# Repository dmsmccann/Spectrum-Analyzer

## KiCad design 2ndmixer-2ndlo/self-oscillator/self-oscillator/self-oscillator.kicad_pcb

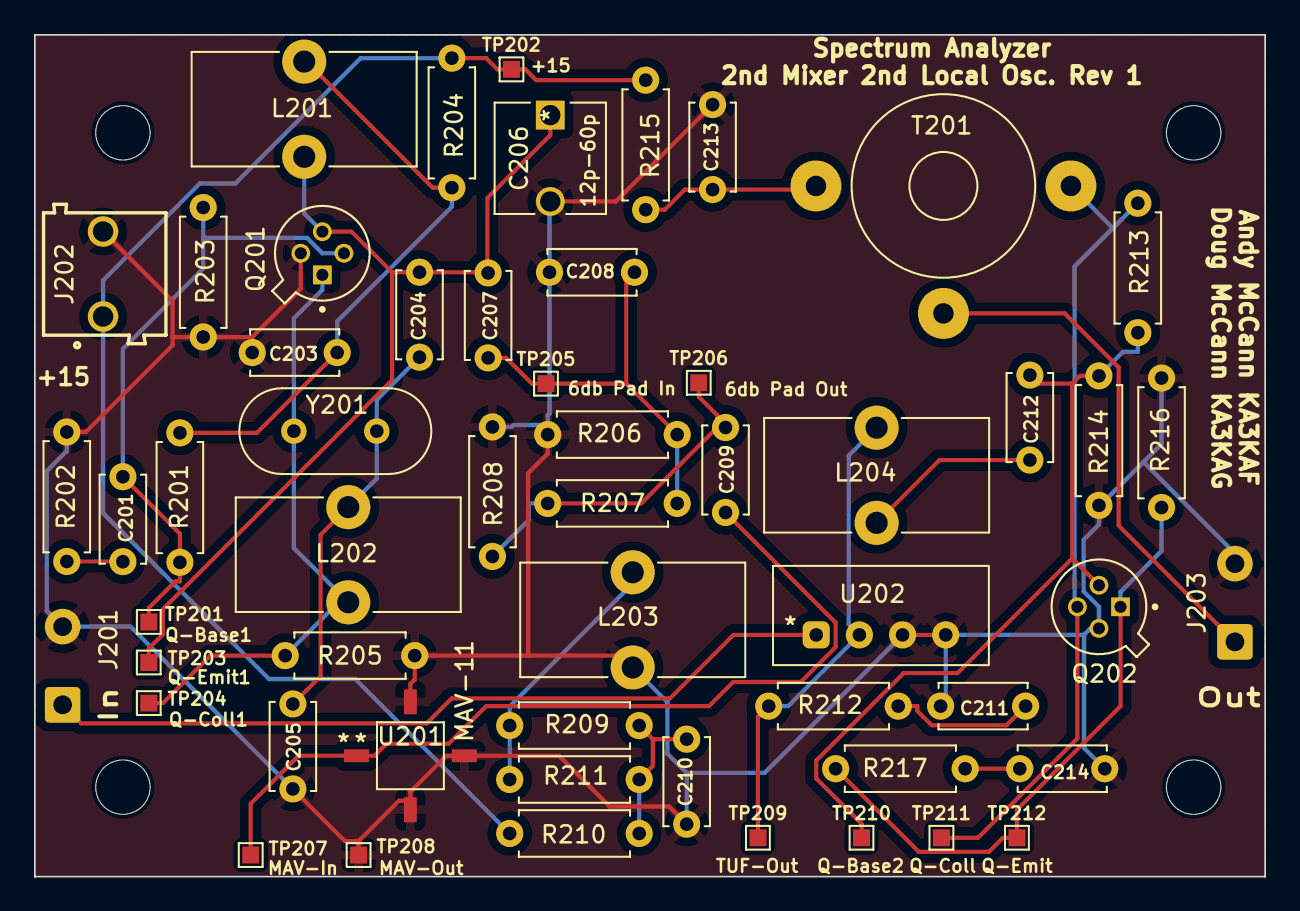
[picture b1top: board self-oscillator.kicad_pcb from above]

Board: 2 copper layers, 72.4 x 49.5 mm, 59 parts (0 on the bottom side), 23 nets.

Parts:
C201, C203: 470p; C_Disc_D5.0mm_W2.5mm_P5.00mm
C204, C205: 33p; C_Disc_D5.0mm_W2.5mm_P5.00mm
C206: 12p-60p; GKG60015
C207: 15p; C_Disc_D5.0mm_W2.5mm_P5.00mm
C208: 82p; C_Disc_D5.0mm_W2.5mm_P5.00mm
C209, C210: .01u; C_Disc_D5.0mm_W2.5mm_P5.00mm
C211: 120p; C_Disc_D5.0mm_W2.5mm_P5.00mm
C212, C213, C214: .1u; C_Disc_D5.0mm_W2.5mm_P5.00mm
H201, H202, H203, H204: MountingHole; MountingHole_3.2mm_M3
J201, J203: Coax Solder Point; SolderWire-0.5sqmm_1x02_P4.6mm_D0.9mm_OD2.1mm
J202: Conn_01x02; 691103110002
L201: 40n; L_Toroid_Vertical_L13.0mm_W6.5mm_P5.60mm
L202: 420n; L_Toroid_Vertical_L13.0mm_W6.5mm_P5.60mm
L203, L204: 1u; L_Toroid_Vertical_L13.0mm_W6.5mm_P5.60mm
Q201, Q202: 2N5179; TO127P584H533-4N
R201: 3.3k; R_Axial_DIN0207_L6.3mm_D2.5mm_P7.62mm_Horizontal
R202: 39; R_Axial_DIN0207_L6.3mm_D2.5mm_P7.62mm_Horizontal
R203, R213: 2k; R_Axial_DIN0207_L6.3mm_D2.5mm_P7.62mm_Horizontal
R204: 100; R_Axial_DIN0207_L6.3mm_D2.5mm_P7.62mm_Horizontal
R205: 510; R_Axial_DIN0207_L6.3mm_D2.5mm_P7.62mm_Horizontal
R206, R208: 150; R_Axial_DIN0207_L6.3mm_D2.5mm_P7.62mm_Horizontal
R207: 36; R_Axial_DIN0207_L6.3mm_D2.5mm_P7.62mm_Horizontal
R209, R211: 220; R_Axial_DIN0207_L6.3mm_D2.5mm_P7.62mm_Horizontal
R210: 47; R_Axial_DIN0207_L6.3mm_D2.5mm_P7.62mm_Horizontal
R212: 51; R_Axial_DIN0207_L6.3mm_D2.5mm_P7.62mm_Horizontal
R214: 390; R_Axial_DIN0207_L6.3mm_D2.5mm_P7.62mm_Horizontal
R215, R216: 27; R_Axial_DIN0207_L6.3mm_D2.5mm_P7.62mm_Horizontal
R217: 5.1; R_Axial_DIN0207_L6.3mm_D2.5mm_P7.62mm_Horizontal
T201: Bifilar_Transformer; Autotransformer_Toroid_1Tap_Horizontal_D10.5mm_Amidon-T37
TP201: Q-Base1; TestPoint_Pad_1.0x1.0mm
TP202: +15; TestPoint_Pad_1.0x1.0mm
TP203: Q-Emit1; TestPoint_Pad_1.0x1.0mm
TP204: Q-Coll1; TestPoint_Pad_1.0x1.0mm
TP205: 6db Pad In; TestPoint_Pad_1.0x1.0mm
TP206: 6db Pad Out; TestPoint_Pad_1.0x1.0mm
TP207: MAV-In; TestPoint_Pad_1.0x1.0mm
TP208: MAV-Out; TestPoint_Pad_1.0x1.0mm
TP209: TUF-Out; TestPoint_Pad_1.0x1.0mm
TP210: Q-Base2; TestPoint_Pad_1.0x1.0mm
TP211: Q-Coll2; TestPoint_Pad_1.0x1.0mm
TP212: Q-Emit2; TestPoint_Pad_1.0x1.0mm
U201: MAV-11; MAV-11BSM&plus_
U202: TUF-1H+; TUF-1H
Y201: 100MHz; Crystal_HC49-U_Vertical

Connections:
/+15: J202.1, R204.1, R210.1, R215.1, TP202.1
GND: C203.2, C205.2, C206.2, C208.2, C210.2, C211.2, C213.1, C214.1, J201.2 (Ext), J202.2, J203.2 (Ext), L203.2, Q201.4 (SHIELD), Q202.4 (SHIELD), R202.2, R203.2, R205.2, R206.2, R208.2, R214.2, R216.2, TP208.1, U201.2 (GND), U201.3 (RF_Out), U201.4 (GND), U202.3 (GND), U202.4 (LO)
unnamed: C201.1, Q201.2, R201.2, R203.1, TP201.1
unnamed: C201.2, R202.1
unnamed: C203.1, L201.1, R201.1, R204.2
unnamed: C204.1, C206.1, C207.1, L201.2, Q201.3, TP203.1
unnamed: C204.2, C205.1, L202.1, Y201.2
unnamed: C207.2, C208.1, R206.1, R207.1, TP205.1
unnamed: C209.1, R207.2, R208.1, TP206.1
unnamed: C210.1, R209.1, R210.2, R211.1
unnamed: C211.1, R212.2
unnamed: C212.1, L204.2
unnamed: C212.2, Q202.2, R213.2, R214.1, TP210.1
unnamed: C213.2, R215.2, T201.1
unnamed: C214.2, R217.2
unnamed: J201.1 (In), U202.1 (RF)
unnamed: J203.1 (In), T201.2
unnamed: L202.2, Q201.1, R205.1, TP204.1, Y201.1
unnamed: L203.1, R209.2, R211.2
unnamed: Q202.1, R216.1, R217.1, TP212.1
unnamed: Q202.3, R213.1, T201.3, TP211.1
unnamed: C209.2, TP207.1, U201.1 (RF_In)
unnamed: L204.1, R212.1, TP209.1, U202.2 (IF)

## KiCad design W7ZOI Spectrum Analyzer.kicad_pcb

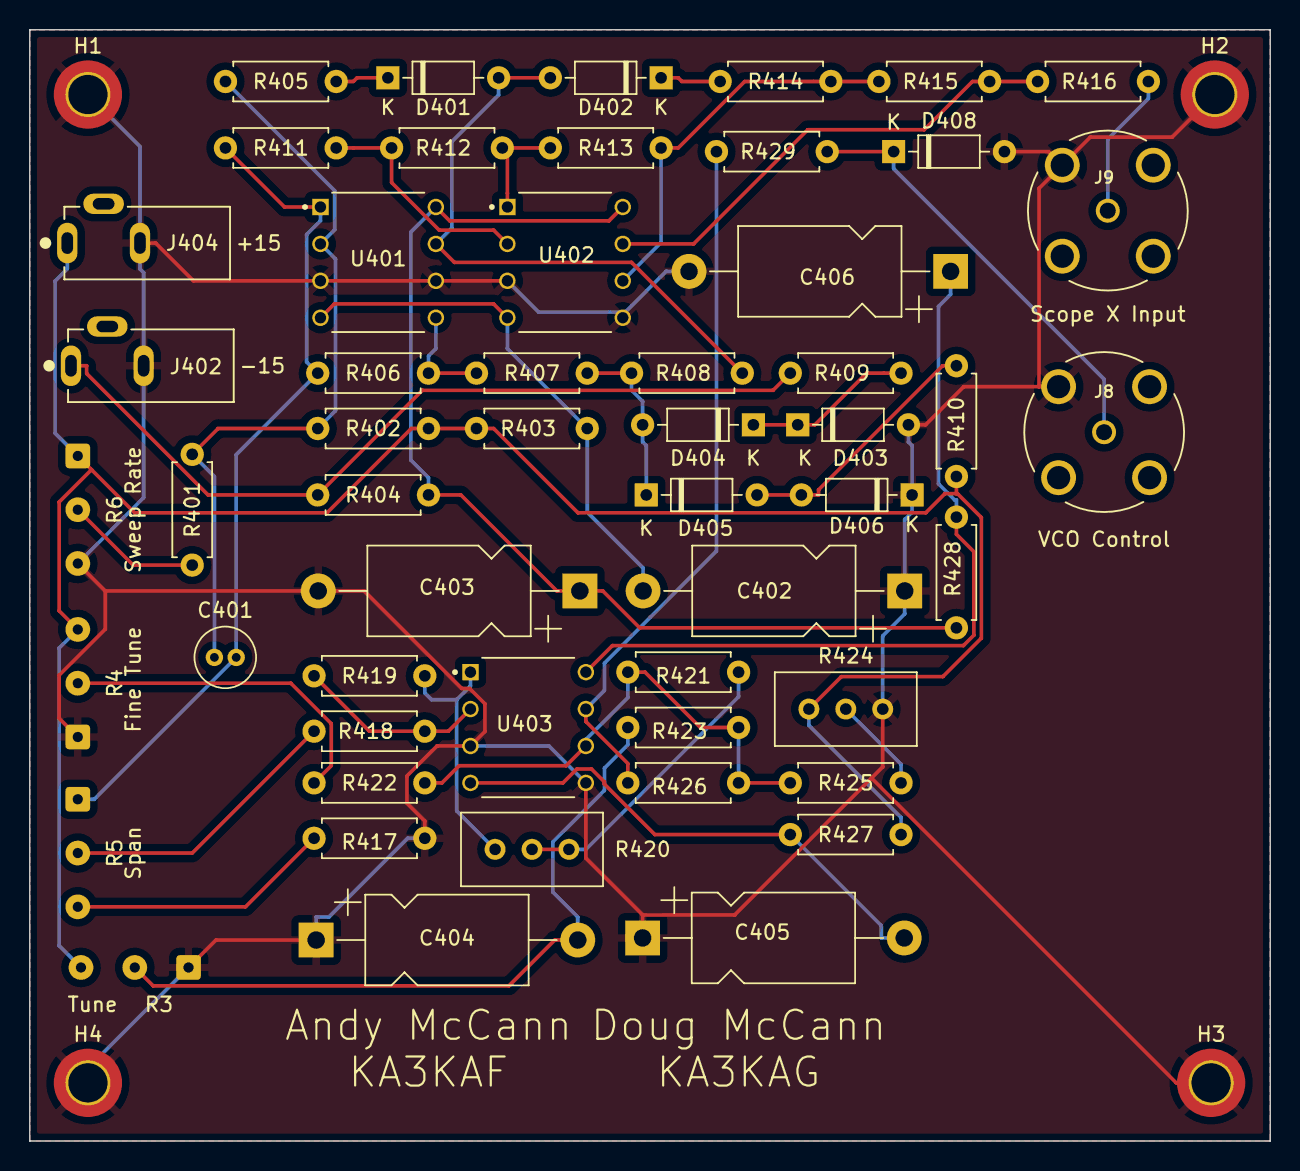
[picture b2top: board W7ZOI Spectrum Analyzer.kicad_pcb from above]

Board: 2 copper layers, 85.3 x 76.5 mm, 57 parts (0 on the bottom side), 33 nets.

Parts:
C401: 1u; C_Radial_D4.0mm_H5.0mm_P1.50mm
C402, C403: 22u; CP_Axial_L11.0mm_D6.0mm_P18.00mm_Horizontal
C404, C405, C406: 100u; CP_Axial_L11.0mm_D6.0mm_P18.00mm_Horizontal
D401, D402, D404, D405, D408: 1N4148; D_DO-35_SOD27_P7.62mm_Horizontal
D403, D406: 1N4735; D_DO-35_SOD27_P7.62mm_Horizontal
H1, H2, H3, H4: MountingHole_Pad; MountingHole_2.7mm_M2.5_DIN965_Pad_TopOnly
J8, J9: Conn_Coaxial; TE_5-1634503-1
J402, J404: Jack-DC; CUI_PJ-007
R3, R4, R6: 10k; SolderWire-0.127sqmm_1x03_P3.7mm_D0.48mm_OD1mm
R5: 5k; SolderWire-0.127sqmm_1x03_P3.7mm_D0.48mm_OD1mm
R401: 56k; R_Axial_DIN0207_L6.3mm_D2.5mm_P7.62mm_Horizontal
R402: 680k; R_Axial_DIN0207_L6.3mm_D2.5mm_P7.62mm_Horizontal
R403, R404: 100; R_Axial_DIN0207_L6.3mm_D2.5mm_P7.62mm_Horizontal
R405, R406, R409, R410: 2.2k; R_Axial_DIN0207_L6.3mm_D2.5mm_P7.62mm_Horizontal
R407: 4.7k; R_Axial_DIN0207_L6.3mm_D2.5mm_P7.62mm_Horizontal
R408: 1k; R_Axial_DIN0207_L6.3mm_D2.5mm_P7.62mm_Horizontal
R411: 12k; R_Axial_DIN0207_L6.3mm_D2.5mm_P7.62mm_Horizontal
R412, R415, R426: 15k; R_Axial_DIN0207_L6.3mm_D2.5mm_P7.62mm_Horizontal
R413, R414, R418, R419, R423, R425: 10k; R_Axial_DIN0207_L6.3mm_D2.5mm_P7.62mm_Horizontal
R416: 390; R_Axial_DIN0207_L6.3mm_D2.5mm_P7.62mm_Horizontal
R417: 51; R_Axial_DIN0207_L6.3mm_D2.5mm_P7.62mm_Horizontal
R420, R424: 5k; Potentiometer_Bourns_3296W_Vertical
R421: 6.8k; R_Axial_DIN0207_L6.3mm_D2.5mm_P7.62mm_Horizontal
R422: 240k; R_Axial_DIN0207_L6.3mm_D2.5mm_P7.62mm_Horizontal
R427, R428: 22; R_Axial_DIN0207_L6.3mm_D2.5mm_P7.62mm_Horizontal
R429: 470; R_Axial_DIN0207_L6.3mm_D2.5mm_P7.62mm_Horizontal
U401, U402, U403: LM358; DIP794W45P254L959H508Q8

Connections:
GND: C402.1, C403.2, C404.1, C405.1, C406.2, D403.2 (A), D406.1 (K), D408.2 (A), H1.1, H2.1, H3.1, H4.1, J8.2 (Ext), J9.2 (Ext), J402.2, J404.2, R3.1, R4.1, R6.3, R417.2, R424.1, U401.3 (+), U401.6 (-), U402.3 (+), U402.5 (+), U403.3 (+), U403.5 (+)
unnamed: C401.1, R401.1, R402.1, R405.1, U401.2 (-)
unnamed: C401.2, R5.1, R406.1, R411.1, U401.1
unnamed: C402.2, R403.1, U401.4 (V-), U402.4 (V-)
unnamed: C403.1, R404.2, R428.1, U401.8 (V+), U402.8 (V+)
unnamed: C404.2, R3.2, R423.2
unnamed: C405.2, R427.1, U403.4 (V-)
unnamed: C406.1, R428.2, U403.8 (V+)
unnamed: D401.1 (K), R405.2
unnamed: D401.2 (A), D402.2 (A), R408.1, U401.7
unnamed: D402.1 (K), R414.1
unnamed: D403.1 (K), D404.1 (K), R409.2
unnamed: D404.2 (A), D405.1 (K), R407.2, R408.2
unnamed: D405.2 (A), D406.2 (A), R410.1
unnamed: R4.2, R422.1
unnamed: R6.2, R401.2
unnamed: R406.2, R407.1, U401.5 (+)
unnamed: R411.2, R412.1, U402.2 (-)
unnamed: R412.2, R413.1, U402.1
unnamed: R413.2, R414.2, R415.1, U402.6 (-)
unnamed: R415.2, R416.1, U402.7
unnamed: R5.3, R417.1
unnamed: R5.2, R418.1
unnamed: R418.2, R419.1, U403.2 (-)
unnamed: R419.2, R420.3, U403.1
unnamed: R420.1, R420.2, R421.1
unnamed: R421.2, R422.2, R423.1, R425.1, R426.1, U403.6 (-)
unnamed: R424.2, R425.2
unnamed: R426.2, R429.1, U403.7
Out: J9.1 (In), R416.2
V+15: J402.1, R404.1, R409.1
V-15: J404.1, R3.3, R4.3, R6.1, R402.2, R403.2, R410.2, R424.3, R427.2
VCO_Out: D408.1 (K), J8.1 (In), R429.2

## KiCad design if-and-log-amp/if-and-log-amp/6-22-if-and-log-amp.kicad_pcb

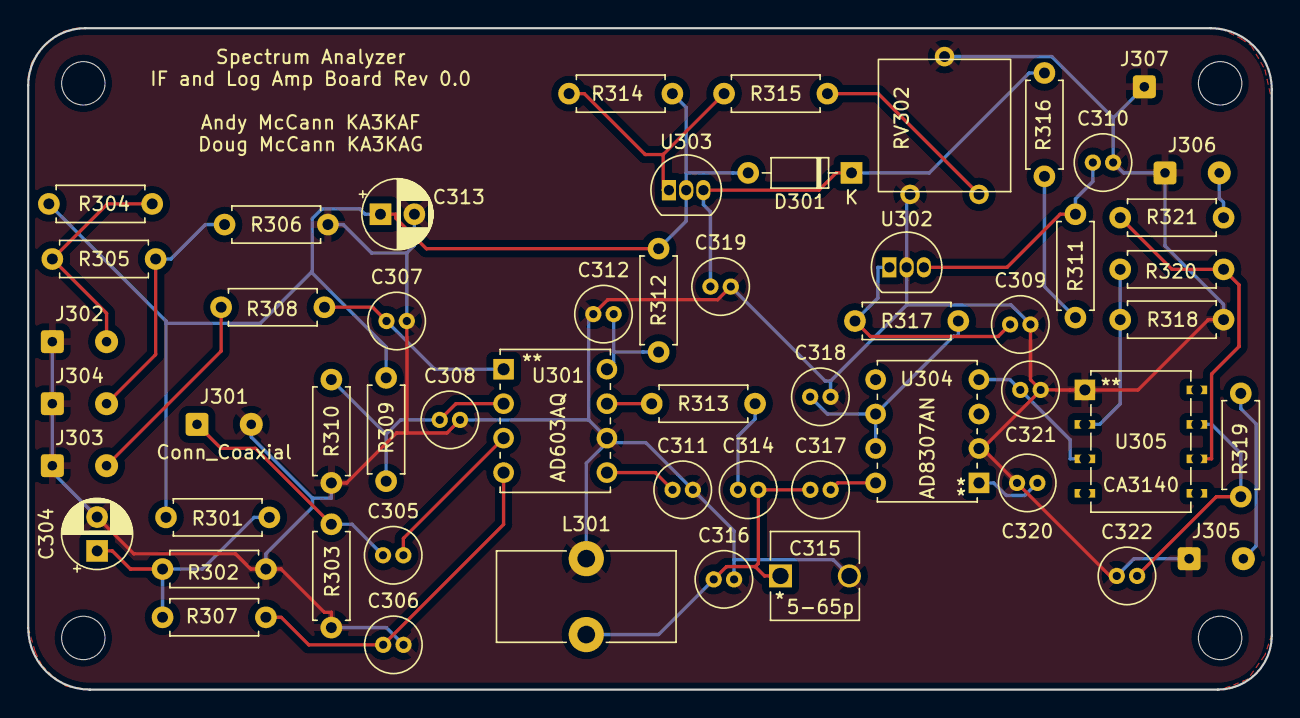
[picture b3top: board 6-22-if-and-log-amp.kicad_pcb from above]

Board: 2 copper layers, 91.7 x 48.8 mm, 59 parts (0 on the bottom side), 31 nets.

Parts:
C304: 100u; CP_Radial_D5.0mm_P2.50mm
C305: .01u; C_Radial_D4.0mm_H5.0mm_P1.50mm
C306, C307, C308, C309, C312, C318, C319, C320, C322: .1u; C_Radial_D4.0mm_H5.0mm_P1.50mm
C310: .22u; C_Radial_D4.0mm_H5.0mm_P1.50mm
C311: 18u; C_Radial_D4.0mm_H5.0mm_P1.50mm
C313: 22u; CP_Radial_D5.0mm_P2.50mm
C314, C317: 5.6p; C_Radial_D4.0mm_H5.0mm_P1.50mm
C315: 5-65p; GKG60015
C316: 220p; C_Radial_D4.0mm_H5.0mm_P1.50mm
C321: .001u; C_Radial_D4.0mm_H5.0mm_P1.50mm
D301: 1N4152; D_DO-35_SOD27_P7.62mm_Horizontal
H301, H302, H303, H304: MountingHole; MountingHole_3.2mm_M3
J301: Conn_Coaxial; SolderWire-0.15sqmm_1x02_P4mm_D0.5mm_OD1.5mm
J302, J303, J304, J305, J306: Conn_01x02_Male; SolderWire-0.15sqmm_1x02_P4mm_D0.5mm_OD1.5mm
J307: Board to Box Ground; SolderWire-0.15sqmm_1x01_D0.5mm_OD1.5mm
L301: 1.05u; L_Toroid_Vertical_L13.0mm_W6.5mm_P5.60mm
R301, R302, R308, R320: 2.2k; R_Axial_DIN0207_L6.3mm_D2.5mm_P7.62mm_Horizontal
R303: 100; R_Axial_DIN0207_L6.3mm_D2.5mm_P7.62mm_Horizontal
R304, R318: 680; R_Axial_DIN0207_L6.3mm_D2.5mm_P7.62mm_Horizontal
R305: 510; R_Axial_DIN0207_L6.3mm_D2.5mm_P7.62mm_Horizontal
R306, R313, R321: 1k; R_Axial_DIN0207_L6.3mm_D2.5mm_P7.62mm_Horizontal
R307, R319: 51; R_Axial_DIN0207_L6.3mm_D2.5mm_P7.62mm_Horizontal
R309: 4.3k; R_Axial_DIN0207_L6.3mm_D2.5mm_P7.62mm_Horizontal
R310: 5.6k; R_Axial_DIN0207_L6.3mm_D2.5mm_P7.62mm_Horizontal
R311, R312, R316, R317: 10; R_Axial_DIN0207_L6.3mm_D2.5mm_P7.62mm_Horizontal
R314: 220; R_Axial_DIN0207_L6.3mm_D2.5mm_P7.62mm_Horizontal
R315: 1.5k; R_Axial_DIN0207_L6.3mm_D2.5mm_P7.62mm_Horizontal
RV302: 100; Potentiometer_Bourns_3386G_Vertical
U301: AD603AQ
U302: L78L05_TO92; TO-92_Inline
U303: LM317L_TO92; TO-92_Inline
U304: AD8307AN
U305: CA3140; CA3140EZ

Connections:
+5: C309.1, R317.1, U302.1 (VO)
+10: C313.1, D301.2 (A), R301.1, R304.1, R309.2, R312.1, R314.1, U303.2 (VO)
+15: R311.1, R316.1
GND: C304.2, C306.2, C307.2, C308.2, C309.2, C310.2, C311.2, C312.1, C313.2, C315.2, C316.2, C318.2, C319.2, C320.1, C321.2, C322.1, J301.2 (Ext), J302.1, J303.1, J304.1, J305.1, J306.1, J307.1, L301.1, R302.2, R303.2, R306.2, R310.2, R318.2, RV302.2, RV302.3, U301.6 (VNEG), U302.2 (GND), U304.2 (COM), U305.1 (NULL)
unnamed: J302.2, R304.2, R305.1
unnamed: J303.2, R308.2
unnamed: J304.2, R305.2, R306.1
unnamed: C304.1, R301.2, R302.1, R307.1
unnamed: C305.1, J301.1 (In), R303.1
unnamed: C305.2, U301.3 (VINP)
unnamed: C306.1, R307.2, U301.4 (COMM)
unnamed: C307.1, R308.1, U301.1 (GPOS)
unnamed: C308.1, R309.1, R310.1, U301.2 (GNEG)
unnamed: C310.1, R311.2, U302.3 (VI)
unnamed: C311.1, U301.5 (FDBK)
unnamed: C312.2, R312.2, U301.8 (VPOS)
unnamed: C314.1, R313.2
unnamed: C314.2, C315.1, C316.1, C317.1, L301.2
unnamed: C317.2, U304.8 (INP)
unnamed: C318.1, R317.2, U304.6 (ENB), U304.7 (VPS)
unnamed: C319.1, D301.1 (K), R316.2, U303.3 (VI)
unnamed: C320.2, U304.1 (INM)
unnamed: C321.1, U304.4 (OUT), U305.3 (+)
unnamed: C322.2, R319.1, U305.7 (V+)
unnamed: J305.2, R319.2
unnamed: R313.1, U301.7 (VOUT)
unnamed: R314.2, R315.1, U303.1 (ADJ)
unnamed: R315.2, RV302.1
unnamed: R318.1, R320.2, U305.2 (-)
unnamed: R320.1, R321.1, U305.6
unnamed: J306.2, R321.2

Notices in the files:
parts and their libraries:
Copyright 2021 Accelerated Designs. All rights reserved.
